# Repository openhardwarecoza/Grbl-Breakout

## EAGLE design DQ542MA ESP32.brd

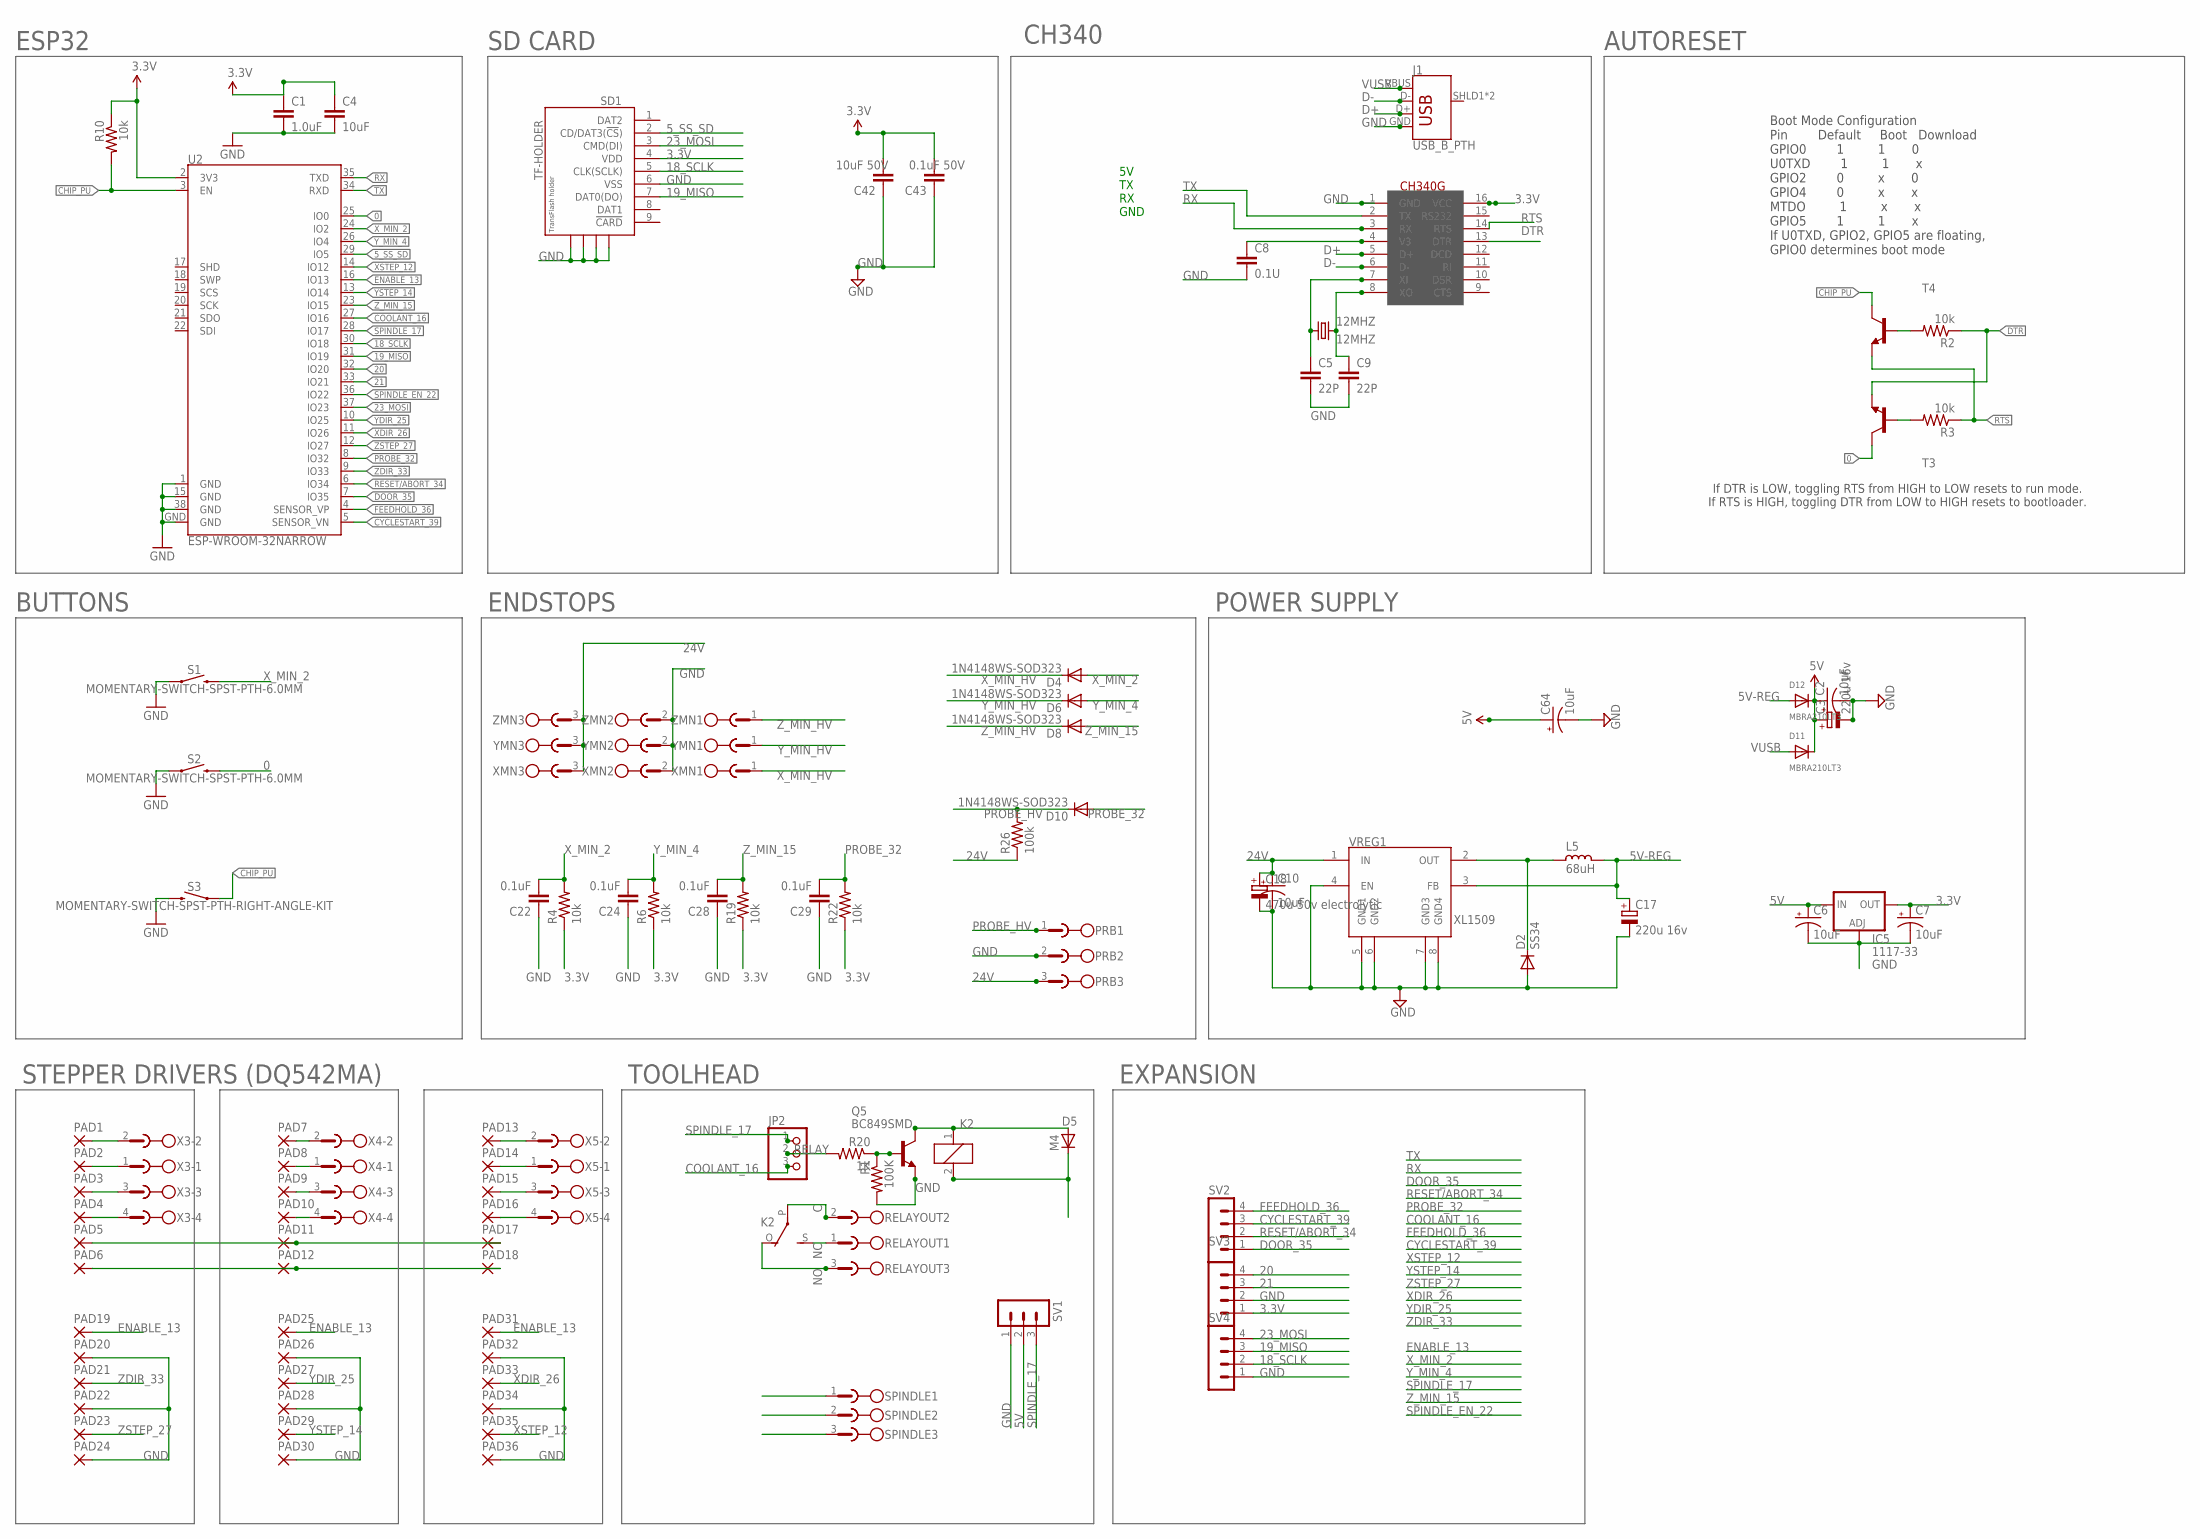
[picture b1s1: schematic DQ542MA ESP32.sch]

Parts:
12MHZ: 12MHZ; HC49U70
C1: 1.0uF; 1206
C2, C6, C7, C10, C64: 10uF; EIA3216
C3, C17: 220u 16v; E3,5-10
C4: 10uF; 1206
C5, C9: 22P; C1206
C8: 0.1U; C1206
C18: 470u 50v electrolytic; E3,5-10
C22, C24, C28, C29: 0.1uF; C1206
C42: 10uF 50V; C1206
C43: 0.1uF 50V; C0603
D2: SS34; DO-214AC
D4, D6, D8, D10: 1N4148WS-SOD323; SOD80C
D5: M4; SOD80
D11, D12: MBRA210LT3; SMADIODE
IC5: 1117-33; SOT223
J1: USB_B_PTH; USB-B-PTH
JP2: PINHD-1X3; 1X03
K2: G5L; G5LE
L5: 68uH; CD75
PAD1, PAD2, PAD3, PAD4, PAD5, PAD6, PAD7, PAD8, PAD9, PAD10, PAD11, PAD12, PAD13, PAD14, PAD15, PAD16, PAD17, PAD18, PAD19, PAD20, PAD21, PAD22, PAD23, PAD24, PAD25, PAD26, PAD27, PAD28, PAD29, PAD30, PAD31, PAD32, PAD33, PAD34, PAD35, PAD36: 3,81/1,4
PRB: Phoenix Pluggable 3.81mm 3 way; MC1.5/3-G-3.81
Q5: BC849SMD; SOT23-BEC
R1: 100K; R1206
R2, R3, R4, R6, R10, R19, R22: 10k; R1206
R20: 1K; R1206
R26: 100k; R1206
RELAYOUT: Phoenix Pluggable 3.81mm 3 way; MC1.5/3-G-3.81
S1, S2: MOMENTARY-SWITCH-SPST-PTH-6.0MM; TACTILE_SWITCH_PTH_6.0MM
S3: MOMENTARY-SWITCH-SPST-PTH-RIGHT-ANGLE-KIT; TACTILE_SWITCH_PTH_RIGHT_ANGLE_KIT
SD1: TF-HOLDER; TF-PULL
SPINDLE: Phoenix Pluggable 3.81mm 3 way; MC1.5/3-G-3.81
SV1: MA03-1
SV2, SV3, SV4: MA04-1
T3, T4: MMBT2222ALT1-NPN-SOT23-BEC; SOT23-BEC
U2: ESP-WROOM-32NARROW; ESP-WROOM-32-NARROW
U$2: CH340G; SOIC16
VREG1: XL1509; SO08
X3, X4, X5: Phoenix Pluggable 3.81mm 4 way; MC1.5/4-G-3.81
XMN: Phoenix Pluggable 3.81mm 3 way; MC1.5/3-G-3.81
YMN: Phoenix Pluggable 3.81mm 3 way; MC1.5/3-G-3.81
ZMN: Phoenix Pluggable 3.81mm 3 way; MC1.5/3-G-3.81

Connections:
0: S2.3 (2), T3.C, U2.25 (IO0)
3.3V: C1.1, C4.1, C7.A (+), C42.2, C43.2, IC5.4 (OUT), R4.1, R6.1, R10.1, R19.1, R22.1, SD1.4 (VDD), SV3.1, U2.2 (3V3), U$2.16 (VCC); also elsewhere on the board
5V: C2.A (+), C3.+, C6.A (+), C64.A (+), D5.1 (C), D11.C, D12.C, IC5.3 (IN), K2.2, SV1.2; also elsewhere on the board
5V-REG: C17.+, D12.A, L5.1, VREG1.3 (FB)
5_SS_SD: SD1.2 (CD/DAT3(!CS!)), U2.29 (IO5)
18_SCLK: SD1.5 (CLK(SCLK)), SV4.2, U2.30 (IO18)
19_MISO: SD1.7 (DAT0(DO)), SV4.3, U2.31 (IO19)
20: SV3.4, U2.32 (IO20)
21: SV3.3, U2.33 (IO21)
23_MOSI: SD1.3 (CMD(DI)), SV4.4, U2.37 (IO23)
24V: C10.A (+), C18.+, PAD6.1, PAD12.1, PAD18.1, PRB.3, R26.1, VREG1.1 (IN), XMN.3, YMN.3, ZMN.3
C: K2.P, RELAYOUT.2
CHIP_PU: R10.2, S3.1, T4.C, U2.3 (EN)
COIL-: D5.2 (A), K2.1, Q5.C
COOLANT_16: JP2.3, U2.27 (IO16)
CYCLESTART_39: SV2.3, U2.5 (SENSOR_VN); also elsewhere on the board
D+: J1.D+, U$2.5 (D+)
D-: J1.D-, U$2.6 (D-)
DOOR_35: SV2.1, U2.7 (IO35); also elsewhere on the board
DTR: R2.1, T3.E, U$2.13 (DTR)
ENABLE_13: PAD19.1, PAD25.1, PAD31.1, U2.16 (IO13)
FEEDHOLD_36: SV2.4, U2.4 (SENSOR_VP); also elsewhere on the board
GND: C1.2, C2.C (-), C3.-, C4.2, C5.2, C6.C (-), C7.C (-), C8.2, C9.2, C10.C (-), C17.-, C18.-, C22.1, C24.1, C28.1, C29.1, C42.1, C43.1, C64.C (-), D2.2 (A), IC5.1 (ADJ), J1.GND, PAD5.1, PAD11.1, PAD17.1, PAD20.1, PAD22.1, PAD24.1, PAD26.1, PAD28.1, PAD30.1, PAD32.1, PAD34.1, PAD36.1, PRB.2, Q5.E, R1.2, S1.1, S2.1, S3.2, SD1.6 (VSS), SD1.S1, SD1.S2, SD1.S3, SD1.S4, SPINDLE.1, SV1.1, SV3.2, SV4.1, U2.1 (GND), U2.15 (GND), U2.38 (GND), U2.GND, U$2.1 (GND), VREG1.4 (EN), VREG1.5 (GND1), VREG1.6 (GND2), VREG1.7 (GND3), VREG1.8 (GND4), XMN.2, YMN.2, ZMN.2; also elsewhere on the board
unnamed: R2.2, T4.B
unnamed: R3.2, T3.B
unnamed: PAD10.1, X4.4
unnamed: PAD8.1, X4.1
unnamed: 12MHZ.1, C5.1, U$2.7 (XI)
unnamed: PAD7.1, X4.2
unnamed: 12MHZ.2, C9.1, U$2.8 (XO)
unnamed: PAD2.1, X3.1
unnamed: PAD1.1, X3.2
unnamed: PAD14.1, X5.1
unnamed: PAD13.1, X5.2
unnamed: PAD4.1, X3.4
unnamed: PAD3.1, X3.3
unnamed: PAD9.1, X4.3
unnamed: PAD16.1, X5.4
unnamed: Q5.B, R1.1, R20.1
unnamed: PAD15.1, X5.3
unnamed: D2.1 (C), L5.2, VREG1.2 (OUT)
NC: K2.S, RELAYOUT.1
NO: K2.O, RELAYOUT.3
PROBE_32: C29.2, D10.A, R22.2, U2.8 (IO32)
PROBE_HV: D10.C, PRB.1, R26.2
RELAY: JP2.2, R20.2
RESET/ABORT_34: SV2.2, U2.6 (IO34); also elsewhere on the board
RTS: R3.1, T4.E, U$2.14 (RTS)
RX: U2.35 (TXD), U$2.3 (RX)
SPINDLE_17: JP2.1, SPINDLE.2, SV1.3, U2.28 (IO17)
SPINDLE_EN_22: SPINDLE.3, U2.36 (IO22)
TX: U2.34 (RXD), U$2.2 (TX)
V3: C8.1, U$2.4 (V3)
VUSB: D11.A, J1.VBUS
XDIR_26: PAD33.1, U2.11 (IO26)
XSTEP_12: PAD35.1, U2.14 (IO12)
X_MIN_2: C22.2, D4.A, R4.2, S1.3 (2), U2.24 (IO2)
X_MIN_HV: D4.C, XMN.1
YDIR_25: PAD27.1, U2.10 (IO25)
YSTEP_14: PAD29.1, U2.13 (IO14)
Y_MIN_4: C24.2, D6.A, R6.2, U2.26 (IO4)
Y_MIN_HV: D6.C, YMN.1
ZDIR_33: PAD21.1, U2.9 (IO33)
ZSTEP_27: PAD23.1, U2.12 (IO27)
Z_MIN_15: C28.2, D8.A, R19.2, U2.23 (IO15)
Z_MIN_HV: D8.C, ZMN.1

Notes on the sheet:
STEPPER DRIVERS (DQ542MA)
ENDSTOPS
POWER SUPPLY
5V TX RX GND
CH340
Boot Mode Configuration Pin Default Boot Download GPIO0 1 1 0 U0TXD 1 1 x GPIO2 0 x 0 GPIO4 0 x x MTDO 1 x x GPIO5 1 1 x If U0TXD, GPIO2, GPIO5 are floating, GPIO0 determines boot mode
If DTR is LOW, toggling RTS from HIGH to LOW resets to run mode. If RTS is HIGH, toggling DTR from LOW to HIGH resets to bootloader.
SD CARD
AUTORESET
ESP32
BUTTONS
TOOLHEAD
EXPANSION

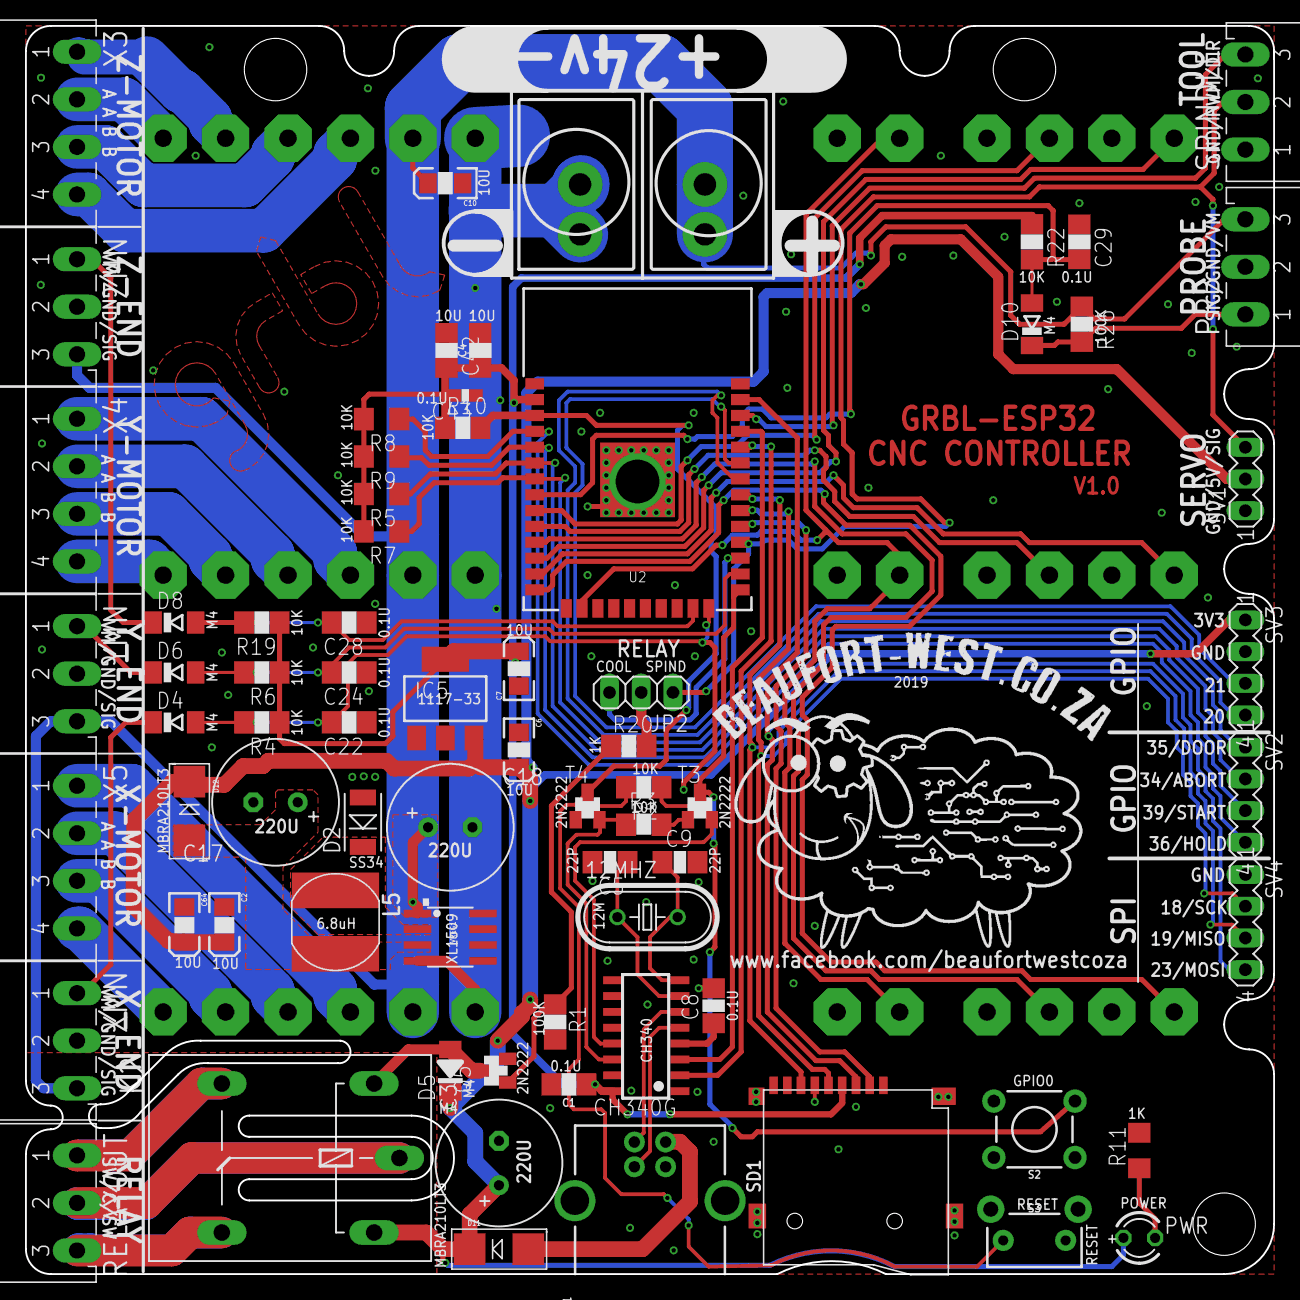
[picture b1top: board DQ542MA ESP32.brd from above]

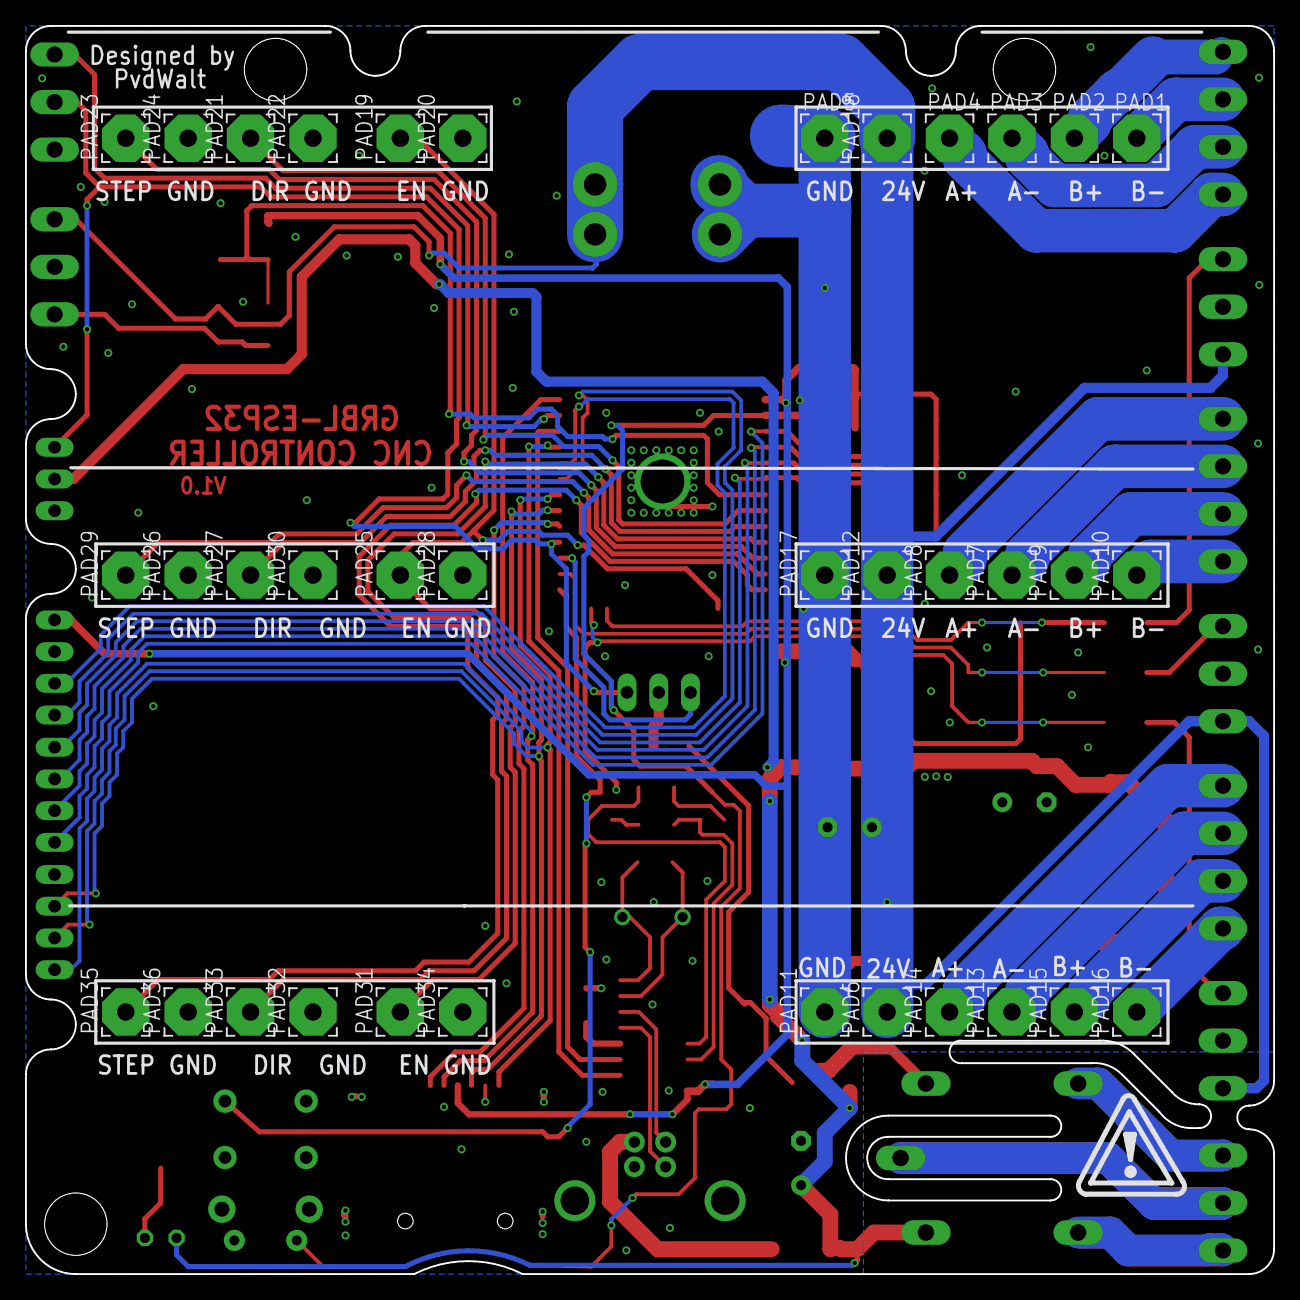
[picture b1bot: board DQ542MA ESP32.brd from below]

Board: 2 copper layers, 100.0 x 100.0 mm, 107 parts (36 on the bottom side), 67 nets.

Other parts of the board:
PWR: LED3MM
R5, R7, R8, R9: 10k; R1206
R11: 1K; R1206

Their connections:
3.3V: R5.2, R7.2, R8.2, R9.2; also elsewhere on the board
5V: PWR.A; also elsewhere on the board
CYCLESTART_39: R9.1; also elsewhere on the board
DOOR_35: R7.1; also elsewhere on the board
FEEDHOLD_36: R8.1; also elsewhere on the board
GND: R11.2; also elsewhere on the board
unnamed: PWR.K, R11.1
RESET/ABORT_34: R5.1; also elsewhere on the board

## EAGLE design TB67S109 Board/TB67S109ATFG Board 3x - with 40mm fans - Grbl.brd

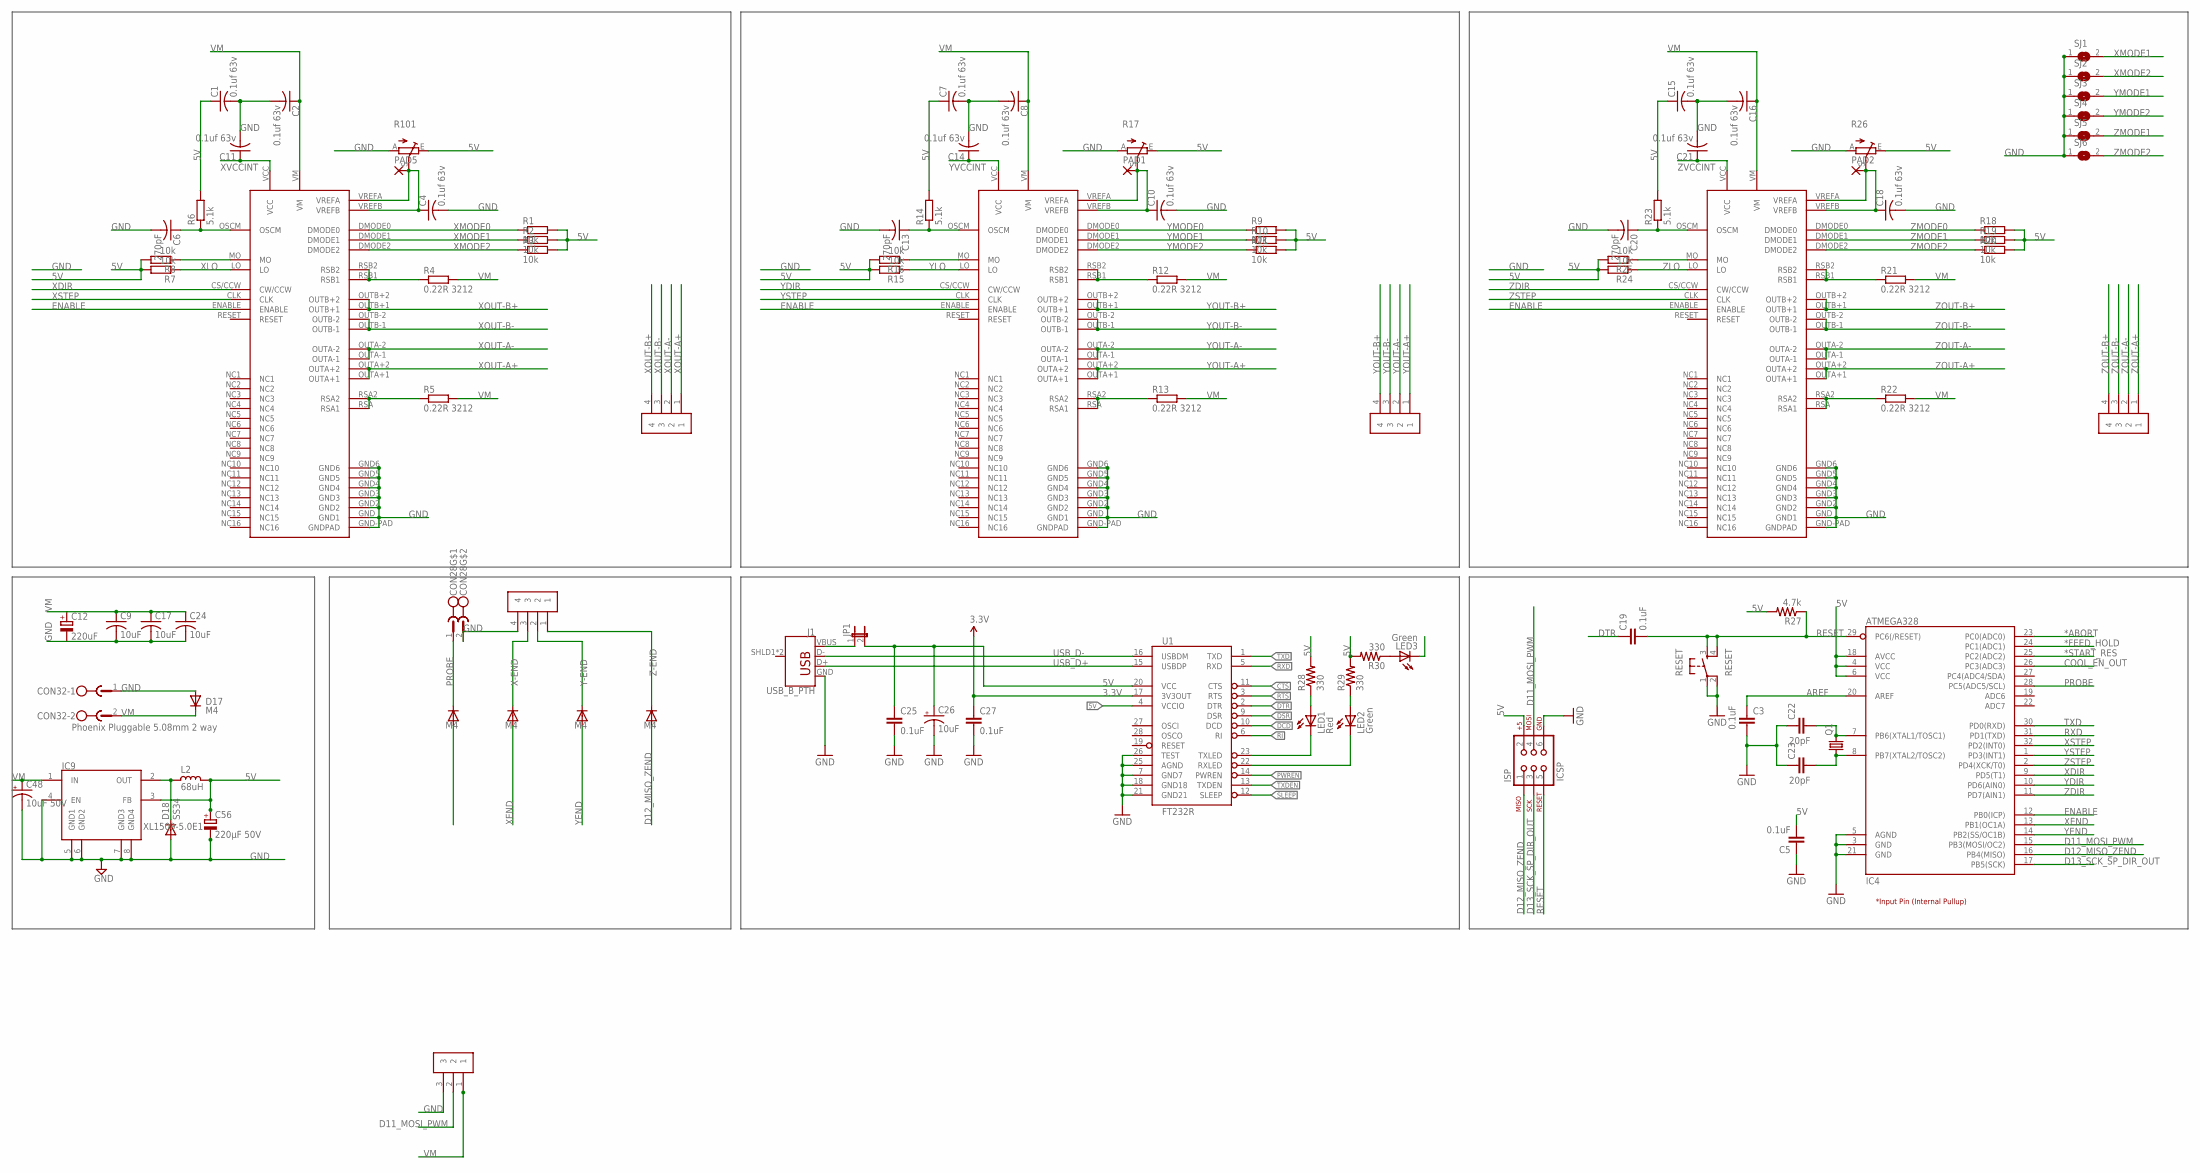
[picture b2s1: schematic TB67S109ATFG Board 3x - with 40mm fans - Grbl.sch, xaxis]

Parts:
C1, C2, C4, C7, C8, C10, C11, C14, C15, C16, C18, C21: 0.1uf 63v; C0603K
C3, C5, C19, C25, C27: 0.1uF; 0603-CAP
C6, C13, C20: 270pF; C0603K
C9, C17, C24: 10uF; C1206K
C12: 220uF; E3,5-8
C22, C23: 20pF; 1206
C26: 10uF; EIA3216
C48: 10uF 50V; EIA3216
C56: 220µF 50V; E3,5-8
CON17: Phoenix Pluggable 3.81mm 3 way; 3.81MM-3WAY-PLUGGABLE-SCREW
CON28: Phoenix Pluggable 3.81mm 2 way; MC1.5/2-G-3.81
CON32: Phoenix Pluggable 5.08mm 2 way; MSTBA2
D2, D14, D15, D16, D17: M4; DO-214AC
D18: SS34; DO-214AC
IC4: ATMEGA328; TQFP32-08
IC9: XL1509-5.0E1; SO08
ISP: ICSP; 2X3
J1: USB_B_PTH; USB-B-PTH
JP1: JP1E; JP1
L2: 68uH; CD75
LED1: Red; LED-0603
LED2, LED3: Green; LED-0603
PAD1, PAD2, PAD5: SMD2; SMD1,27-2,54
Q1: CRYSTALHC49S; HC49/S
R1, R2, R3, R7, R8, R9, R10, R11, R15, R16, R18, R19, R20, R24, R25: 10k; R0603
R4, R5, R12, R13, R21, R22: 0.22R 3212; R1210
R6, R14, R23: 5.1k; R0603
R17, R26, R101: TRIM_EU-B25P; B25P
R27: 4.7k; R0603
R28, R29, R30: 330; 0603-RES
RESET: RESET; TACTILE-PTH
SJ1, SJ2, SJ3, SJ4, SJ5, SJ6: SJ
U1: FT232R; SSOP28DB
U$1, U$4, U$17: TB67S109AFTG; TB67S109AFTG-HTSSPO48-P-300-0.50
U$2, U$3, U$5, U$7: CONNECTOR-M4; 3.81MM-4WAY-PLUGGABLE-SCREW

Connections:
3.3V: C27.1, U1.17 (3V3OUT)
5V: C1.1, C5.2, C7.1, C15.1, C25.1, C26.A (+), C56.+, IC4.4 (VCC), IC4.6 (VCC), IC4.18 (AVCC), IC9.3 (FB), ISP.2, JP1.2, L2.1, R1.2, R2.2, R3.2, R6.2, R7.2, R8.2, R9.2, R10.2, R11.2, R14.2, R15.2, R16.2, R17.E, R18.2, R19.2, R20.2, R23.2, R24.2, R25.2, R26.E, R27.2, R28.2, R29.2, R30.2, R101.E, U1.4 (VCCIO), U1.20 (VCC)
*ABORT: IC4.23 (PC0(ADC0))
*FEED_HOLD: IC4.24 (PC1(ADC1))
*START_RES: IC4.25 (PC2(ADC2))
AREF: C3.1, IC4.20 (AREF)
COOL_EN_OUT: IC4.26 (PC3(ADC3))
CTS: U1.11 (CTS)
D11_MOSI_PWM: CON17.2, IC4.15 (PB3(MOSI/OC2)), ISP.4
D12_MISO_ZEND: D16.A, IC4.16 (PB4(MISO)), ISP.1
D13_SCK_SP_DIR_OUT: IC4.17 (PB5(SCK)), ISP.3
DCD: U1.10 (DCD)
DSR: U1.9 (DSR)
DTR: C19.1, U1.2 (DTR)
ENABLE: IC4.12 (PB0(ICP)), U$1.ENABLE, U$4.ENABLE, U$17.ENABLE
GND: C1.2, C2.2, C3.2, C4.2, C5.1, C6.2, C7.2, C8.2, C9.2, C10.2, C11.2, C12.-, C13.2, C14.2, C15.2, C16.2, C17.2, C18.2, C20.2, C21.2, C22.1, C23.1, C24.2, C25.2, C26.C (-), C27.2, C48.C (-), C56.-, CON17.3, CON28.2, CON32.1, D17.A, D18.2 (A), IC4.3 (GND), IC4.5 (AGND), IC4.21 (GND), IC9.4 (EN), IC9.5 (GND1), IC9.6 (GND2), IC9.7 (GND3), IC9.8 (GND4), ISP.6, J1.GND, LED3.C, R17.A, R26.A, R101.A, RESET.1, RESET.2, SJ1.1, SJ2.1, SJ3.1, SJ4.1, SJ5.1, SJ6.1, U1.7 (GND7), U1.18 (GND18), U1.21 (GND21), U1.25 (AGND), U1.26 (TEST), U$1.GND (GND1), U$1.GND2, U$1.GND3, U$1.GND4, U$1.GND5, U$1.GND6, U$1.GND-PAD (GNDPAD), U$4.GND (GND1), U$4.GND2, U$4.GND3, U$4.GND4, U$4.GND5, U$4.GND6, U$4.GND-PAD (GNDPAD), U$7.4, U$17.GND (GND1), U$17.GND2, U$17.GND3, U$17.GND4, U$17.GND5, U$17.GND6, U$17.GND-PAD (GNDPAD)
unnamed: LED1.A, R28.1
unnamed: LED2.A, R29.1
unnamed: J1.VBUS, JP1.1
unnamed: D18.1 (C), IC9.2 (OUT), L2.2
unnamed: LED3.A, R30.1
unnamed: C22.2, IC4.7 (PB6(XTAL1/TOSC1)), Q1.2
unnamed: C23.2, IC4.8 (PB7(XTAL2/TOSC2)), Q1.1
P0W: C4.1, PAD5.1, R101.S, U$17.VREFA, U$17.VREFB
P0W1: C10.1, PAD1.1, R17.S, U$1.VREFA, U$1.VREFB
P0W2: C18.1, PAD2.1, R26.S, U$4.VREFA, U$4.VREFB
PROBE: D2.A, IC4.28 (PC5(ADC5/SCL))
PROBE-IN: CON28.1, D2.C
PWREN: U1.14 (PWREN)
RESET: C19.2, IC4.29 (PC6(/RESET)), ISP.5, R27.1, RESET.3, RESET.4
RI: U1.6 (RI)
RTS: U1.3 (RTS)
RXD: IC4.31 (PD1(TXD)), U1.5 (RXD)
RXLED: LED2.C, U1.22 (RXLED)
SLEEP: U1.12 (SLEEP)
TXD: IC4.30 (PD0(RXD)), U1.1 (TXD)
TXDEN: U1.13 (TXDEN)
TXLED: LED1.C, U1.23 (TXLED)
USB_D+: J1.D+, U1.15 (USBDP)
USB_D-: J1.D-, U1.16 (USBDM)
VM: C2.1, C8.1, C9.1, C12.+, C16.1, C17.1, C24.1, C48.A (+), CON17.1, CON32.2, D17.C, IC9.1 (IN), R4.2, R5.2, R12.2, R13.2, R21.2, R22.2, U$1.VM, U$4.VM, U$17.VM
X-END: D14.C, U$7.3
XDIR: IC4.9 (PD5(T1)), U$17.CS/CCW (CW/CCW)
XEND: D14.A, IC4.13 (PB1(OC1A))
XLO: R7.1, U$17.LO
XMO: R8.1, U$17.MO
XMO1: R16.1, U$1.MO
XMO2: R25.1, U$4.MO
XMODE0: R1.1, U$17.DMODE0
XMODE1: R2.1, SJ1.2, U$17.DMODE1
XMODE2: R3.1, SJ2.2, U$17.DMODE2
XOSCM: C6.1, R6.1, U$17.OSCM
XOSCM1: C13.1, R14.1, U$1.OSCM
XOSCM2: C20.1, R23.1, U$4.OSCM
XOUT-A+: U$2.1, U$17.OUTA+1, U$17.OUTA+2
XOUT-A-: U$2.2, U$17.OUTA-1, U$17.OUTA-2
XOUT-B+: U$2.4, U$17.OUTB+1, U$17.OUTB+2
XOUT-B-: U$2.3, U$17.OUTB-1, U$17.OUTB-2
XRSA: R5.1, U$17.RSA (RSA1), U$17.RSA2
XRSA1: R13.1, U$1.RSA (RSA1), U$1.RSA2
XRSA2: R22.1, U$4.RSA (RSA1), U$4.RSA2
XRSB: R4.1, U$17.RSB1, U$17.RSB2
XRSB1: R12.1, U$1.RSB1, U$1.RSB2
XRSB2: R21.1, U$4.RSB1, U$4.RSB2
XSTEP: IC4.32 (PD2(INT0)), U$17.CLK
XVCCINT: C11.1, U$17.VCC
Y-END: D15.C, U$7.2
YDIR: IC4.10 (PD6(AIN0)), U$1.CS/CCW (CW/CCW)
YEND: D15.A, IC4.14 (PB2(SS/OC1B))
YLO: R15.1, U$1.LO
YMODE0: R9.1, U$1.DMODE0
YMODE1: R10.1, SJ3.2, U$1.DMODE1
YMODE2: R11.1, SJ4.2, U$1.DMODE2
YOUT-A+: U$1.OUTA+1, U$1.OUTA+2, U$3.1
YOUT-A-: U$1.OUTA-1, U$1.OUTA-2, U$3.2
YOUT-B+: U$1.OUTB+1, U$1.OUTB+2, U$3.4
YOUT-B-: U$1.OUTB-1, U$1.OUTB-2, U$3.3
YSTEP: IC4.1 (PD3(INT1)), U$1.CLK
YVCCINT: C14.1, U$1.VCC
Z-END: D16.C, U$7.1
ZDIR: IC4.11 (PD7(AIN1)), U$4.CS/CCW (CW/CCW)
ZLO: R24.1, U$4.LO
ZMODE0: R18.1, U$4.DMODE0
ZMODE1: R19.1, SJ5.2, U$4.DMODE1
ZMODE2: R20.1, SJ6.2, U$4.DMODE2
ZOUT-A+: U$4.OUTA+1, U$4.OUTA+2, U$5.1
ZOUT-A-: U$4.OUTA-1, U$4.OUTA-2, U$5.2
ZOUT-B+: U$4.OUTB+1, U$4.OUTB+2, U$5.4
ZOUT-B-: U$4.OUTB-1, U$4.OUTB-2, U$5.3
ZSTEP: IC4.2 (PD4(XCK/T0)), U$4.CLK
ZVCCINT: C21.1, U$4.VCC

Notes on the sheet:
*Input Pin (Internal Pullup)

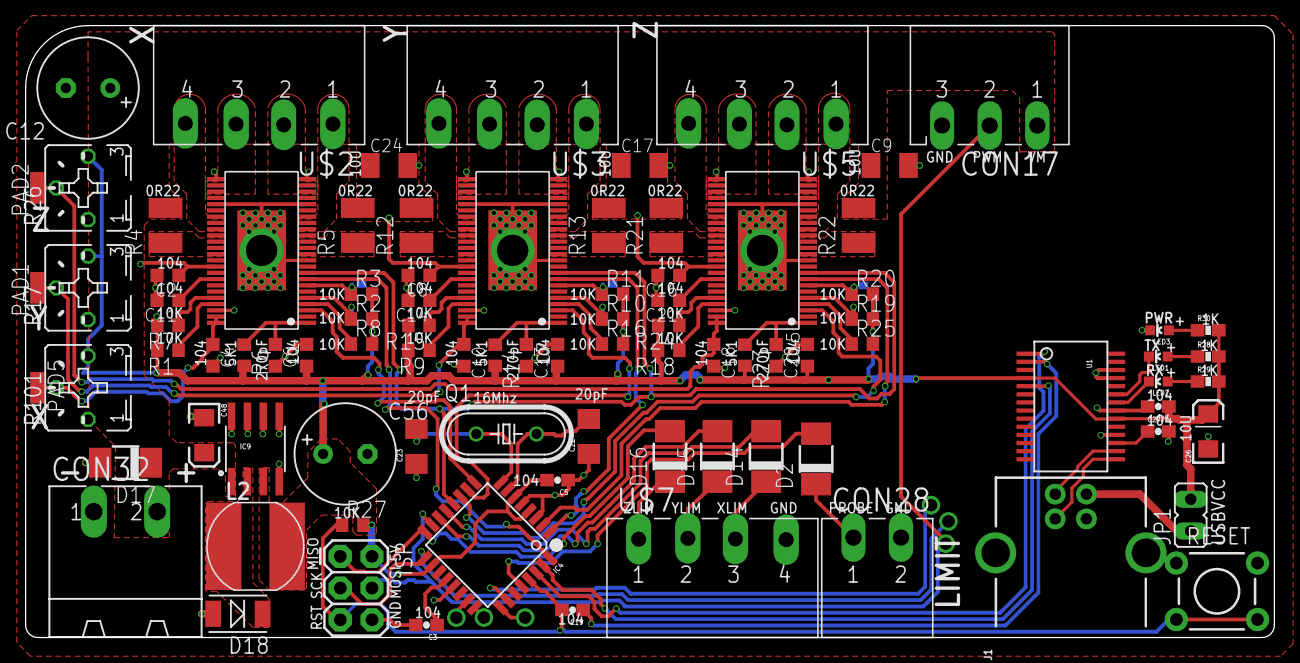
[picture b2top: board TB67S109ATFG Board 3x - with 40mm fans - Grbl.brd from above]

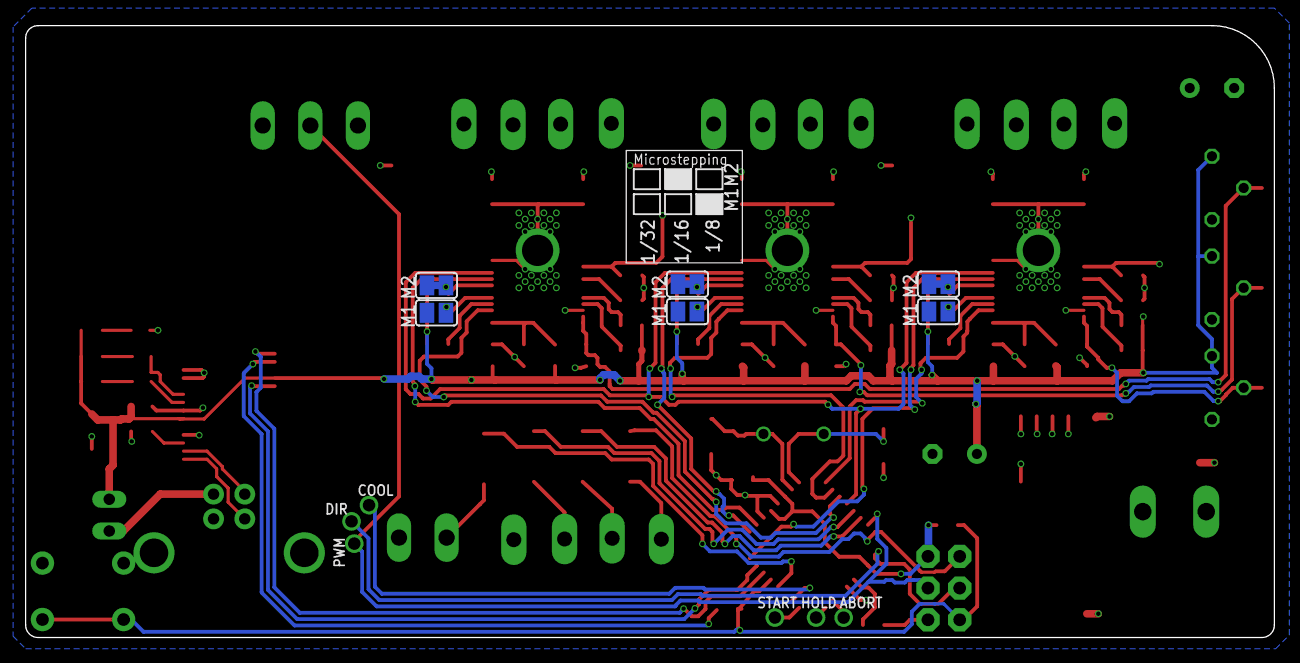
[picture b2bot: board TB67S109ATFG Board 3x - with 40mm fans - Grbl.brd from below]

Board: 2 copper layers, 100.0 x 49.0 mm, 97 parts (6 on the bottom side), 79 nets.

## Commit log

2018-05-01 First
2018-05-01 untested gerbers
2018-10-23 archive
2019-08-01 ESP32
2019-09-12 Post assembly notes

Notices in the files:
parts and their libraries:
rc-master-smd: Copyright (C) 2007, Bob Starr
SparkFun-Connectors: Licensing: Creative Commons ShareAlike 4.0 International - https://creativecommons.org/licenses/by-sa/4.0
SparkFun-Aesthetics: Licensing: CC v3.0 Share-Alike You are welcome to use this library for commercial purposes.
